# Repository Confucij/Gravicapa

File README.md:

Gravicapa
=========
Универсальное устройства для слежения за аудиториями, сбора различной информации, её обработки и отображения.

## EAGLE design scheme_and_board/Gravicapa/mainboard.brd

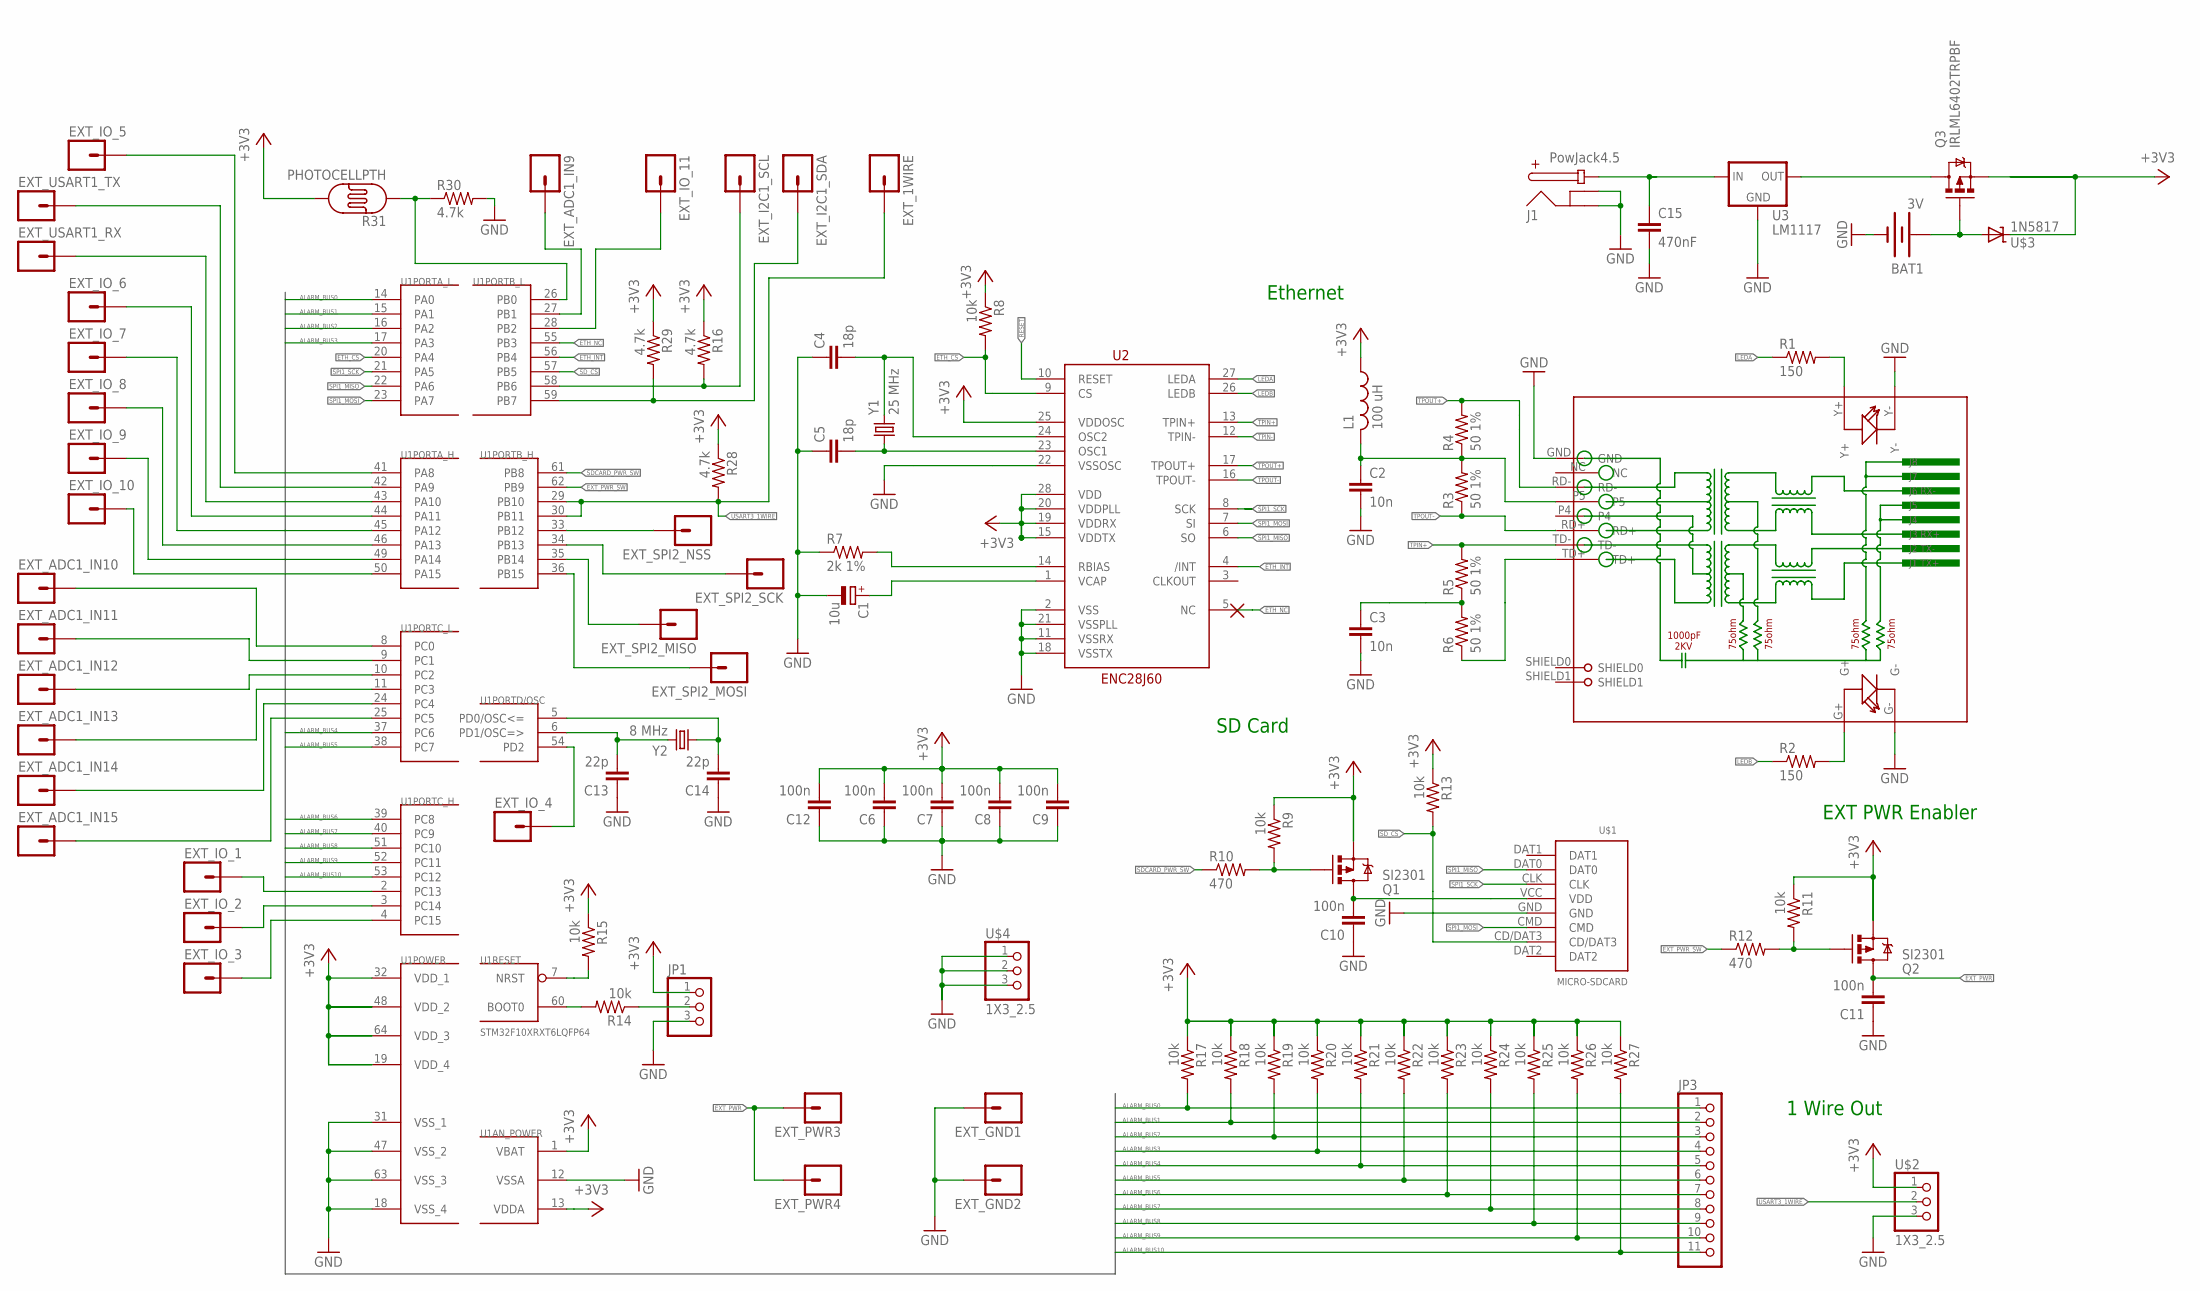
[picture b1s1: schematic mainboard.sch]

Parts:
BAT1: 3V; BATTCOM_20MM_PTH
C1: 10u; SMC_B
C2, C3: 10n; 0805
C4, C5: 18p; 0805
C6, C7, C8, C9, C10, C11, C12: 100n; 0805
C13, C14: 22p; 0805
C15: 470nF; C1206
EXT_1WIRE: M01PTH; 1X01
EXT_ADC1_IN9, EXT_ADC1_IN10, EXT_ADC1_IN11, EXT_ADC1_IN12, EXT_ADC1_IN13, EXT_ADC1_IN14, EXT_ADC1_IN15: M01PTH; 1X01
EXT_GND1, EXT_GND2: M01PTH; 1X01
EXT_I2C1_SCL, EXT_I2C1_SDA: M01PTH; 1X01
EXT_IO_1, EXT_IO_2, EXT_IO_3, EXT_IO_4, EXT_IO_5, EXT_IO_6, EXT_IO_7, EXT_IO_8, EXT_IO_9, EXT_IO_10, EXT_IO_11: M01PTH; 1X01
EXT_PWR3, EXT_PWR4: M01PTH; 1X01
EXT_SPI2_MISO, EXT_SPI2_MOSI, EXT_SPI2_NSS, EXT_SPI2_SCK: M01PTH; 1X01
EXT_USART1_RX, EXT_USART1_TX: M01PTH; 1X01
J1: PowJack4.5; POWER_JACK_4.5
JP1: PINHD-1X3; 1X03
JP3: PINHD-1X11; 1X11
L1: 100 uH; POWER-CHOKE_WE-TPC
Q1, Q2: SI2301; SOT23-3
Q3: IRLML6402TRPBF; SOT23-3
R1, R2: 150; 0805
R3, R4, R5, R6: 50 1%; 0805
R7: 2k 1%; 0805
R8, R9, R11, R13, R14, R15, R17, R18, R19, R20, R21, R22, R23, R24, R25, R26, R27: 10k; 0805
R10, R12: 470; 0805
R16, R28, R29, R30: 4.7k; 0805
R31: PHOTOCELLPTH; PHOTOCELL
RJ1: HR911105A
U1: STM32F10XRXT6LQFP64; LQFP64_MILL
U2: ENC28J60; SSOP28DB
U3: LM1117; DPAK
U$1: MICRO-SDCARD
U$2, U$4: 1X3_2.5
U$3: 1N5817; DIODE-ZENER
Y1: 25 MHz; HC49U-V
Y2: 8 MHz; HC49U-V

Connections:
+3V3: C6.2, C7.2, C8.2, C9.2, C12.2, JP1.1, L1.1, Q1.2 (S), Q2.2 (S), Q3.2 (S), R8.1, R9.1, R11.1, R13.1, R15.1, R16.1, R17.1, R18.1, R19.1, R20.1, R21.1, R22.1, R23.1, R24.1, R25.1, R26.1, R27.1, R28.1, R29.1, R31.2, U1.1 (VBAT), U1.13 (VDDA), U1.19 (VDD_4), U1.32 (VDD_1), U1.48 (VDD_2), U1.64 (VDD_3), U2.15 (VDDTX), U2.19 (VDDRX), U2.20 (VDDPLL), U2.25 (VDDOSC), U2.28 (VDD), U$2.1, U$3.P$1 (C)
ALARM_BUS0: JP3.1, R17.2, U1.14 (PA0)
ALARM_BUS1: JP3.2, R18.2, U1.15 (PA1)
ALARM_BUS2: JP3.3, R19.2, U1.16 (PA2)
ALARM_BUS3: JP3.4, R20.2, U1.17 (PA3)
ALARM_BUS4: JP3.5, R21.2, U1.37 (PC6)
ALARM_BUS5: JP3.6, R22.2, U1.38 (PC7)
ALARM_BUS6: JP3.7, R23.2, U1.39 (PC8)
ALARM_BUS7: JP3.8, R24.2, U1.40 (PC9)
ALARM_BUS8: JP3.9, R25.2, U1.51 (PC10)
ALARM_BUS9: JP3.10, R26.2, U1.52 (PC11)
ALARM_BUS10: JP3.11, R27.2, U1.53 (PC12)
ETH_CS: R8.2, U1.20 (PA4), U2.9 (CS)
ETH_INT: U1.56 (PB4), U2.4 (/INT)
ETH_NC: U1.55 (PB3), U2.5 (NC)
EXT_PWR: C11.2, EXT_PWR3.1, EXT_PWR4.1, Q2.3 (D)
EXT_PWR_SW: R12.1, U1.62 (PB9)
GND: BAT1.2 (-), C1.-, C2.2, C3.2, C4.1, C5.1, C6.1, C7.1, C8.1, C9.1, C10.1, C11.1, C12.1, C13.1, C14.1, C15.2, EXT_GND1.1, EXT_GND2.1, J1.GND@1 (GND), J1.GND@2 (GNDBREAK), JP1.3, R7.1, R30.2, RJ1.G-, RJ1.GND, RJ1.Y-, U1.12 (VSSA), U1.18 (VSS_4), U1.31 (VSS_1), U1.47 (VSS_2), U1.63 (VSS_3), U2.2 (VSS), U2.11 (VSSRX), U2.18 (VSSTX), U2.21 (VSSPLL), U2.22 (VSSOSC), U3.1 (GND), U$1.GND, U$2.3, U$4.1, U$4.2, U$4.3
I2C1_SCL: EXT_I2C1_SCL.1, R16.2, U1.58 (PB6)
I2C1_SDA: EXT_I2C1_SDA.1, R29.2, U1.59 (PB7)
LEDA: R1.1, U2.27 (LEDA)
LEDB: R2.1, U2.26 (LEDB)
unnamed: C2.1, L1.2, R3.2, R4.1, RJ1.P5
unnamed: R2.2, RJ1.G+
unnamed: R1.2, RJ1.Y+
unnamed: R7.2, U2.14 (RBIAS)
unnamed: C5.2, U2.23 (OSC1), Y1.1
unnamed: C4.2, U2.24 (OSC2), Y1.2
unnamed: C1.+, U2.1 (VCAP)
unnamed: Q2.1 (G), R11.2, R12.2
unnamed: C3.1, R5.1, R6.2
unnamed: Q1.1 (G), R9.2, R10.2
unnamed: C10.2, Q1.3 (D), U$1.VCC (VDD)
unnamed: EXT_IO_1.1, U1.2 (PC13)
unnamed: R14.2, U1.60 (BOOT0)
unnamed: JP1.2, R14.1
unnamed: R15.2, U1.7 (NRST)
unnamed: C14.2, U1.5 (PD0/OSC<=), Y2.1
unnamed: C13.2, U1.6 (PD1/OSC=>), Y2.2
unnamed: C15.1, J1.PWR, U3.3 (IN)
unnamed: EXT_IO_2.1, U1.3 (PC14)
unnamed: EXT_IO_3.1, U1.4 (PC15)
unnamed: EXT_IO_4.1, U1.54 (PD2)
unnamed: EXT_IO_5.1, U1.41 (PA8)
unnamed: EXT_USART1_TX.1, U1.42 (PA9)
unnamed: EXT_USART1_RX.1, U1.43 (PA10)
unnamed: EXT_IO_6.1, U1.44 (PA11)
unnamed: EXT_IO_7.1, U1.45 (PA12)
unnamed: EXT_IO_8.1, U1.46 (PA13)
unnamed: EXT_IO_9.1, U1.49 (PA14)
unnamed: EXT_IO_10.1, U1.50 (PA15)
unnamed: R30.1, R31.1, U1.26 (PB0)
unnamed: EXT_ADC1_IN9.1, U1.27 (PB1)
unnamed: EXT_ADC1_IN15.1, U1.25 (PC5)
unnamed: EXT_ADC1_IN14.1, U1.24 (PC4)
unnamed: EXT_ADC1_IN13.1, U1.11 (PC3)
unnamed: EXT_ADC1_IN12.1, U1.10 (PC2)
unnamed: EXT_ADC1_IN11.1, U1.9 (PC1)
unnamed: EXT_ADC1_IN10.1, U1.8 (PC0)
unnamed: BAT1.1 (+), Q3.1 (G), U$3.P$2 (A)
unnamed: EXT_IO_11.1, U1.28 (PB2)
unnamed: Q3.3 (D), U3.4 (OUT)
RESET: U2.10 (RESET)
SDCARD_PWR_SW: R10.1, U1.61 (PB8)
SD_CS: R13.2, U1.57 (PB5), U$1.CD/DAT3
SPI1_MISO: U1.22 (PA6), U2.6 (SO), U$1.DAT0
SPI1_MOSI: U1.23 (PA7), U2.7 (SI), U$1.CMD
SPI1_SCK: U1.21 (PA5), U2.8 (SCK), U$1.CLK
SPI2_MISO: EXT_SPI2_MISO.1, U1.35 (PB14)
SPI2_MOSI: EXT_SPI2_MOSI.1, U1.36 (PB15)
SPI2_NSS: EXT_SPI2_NSS.1, U1.33 (PB12)
SPI2_SCK: EXT_SPI2_SCK.1, U1.34 (PB13)
TPIN+: R5.2, RJ1.TD-, U2.13 (TPIN+)
TPIN-: R6.1, RJ1.TD+, U2.12 (TPIN-)
TPOUT+: R4.2, RJ1.RD-, U2.17 (TPOUT+)
TPOUT-: R3.1, RJ1.RD+, U2.16 (TPOUT-)
USART3_1WIRE: EXT_1WIRE.1, R28.2, U1.29 (PB10), U1.30 (PB11), U$2.2

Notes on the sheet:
Ethernet
EXT PWR Enabler
SD Card
1 Wire Out

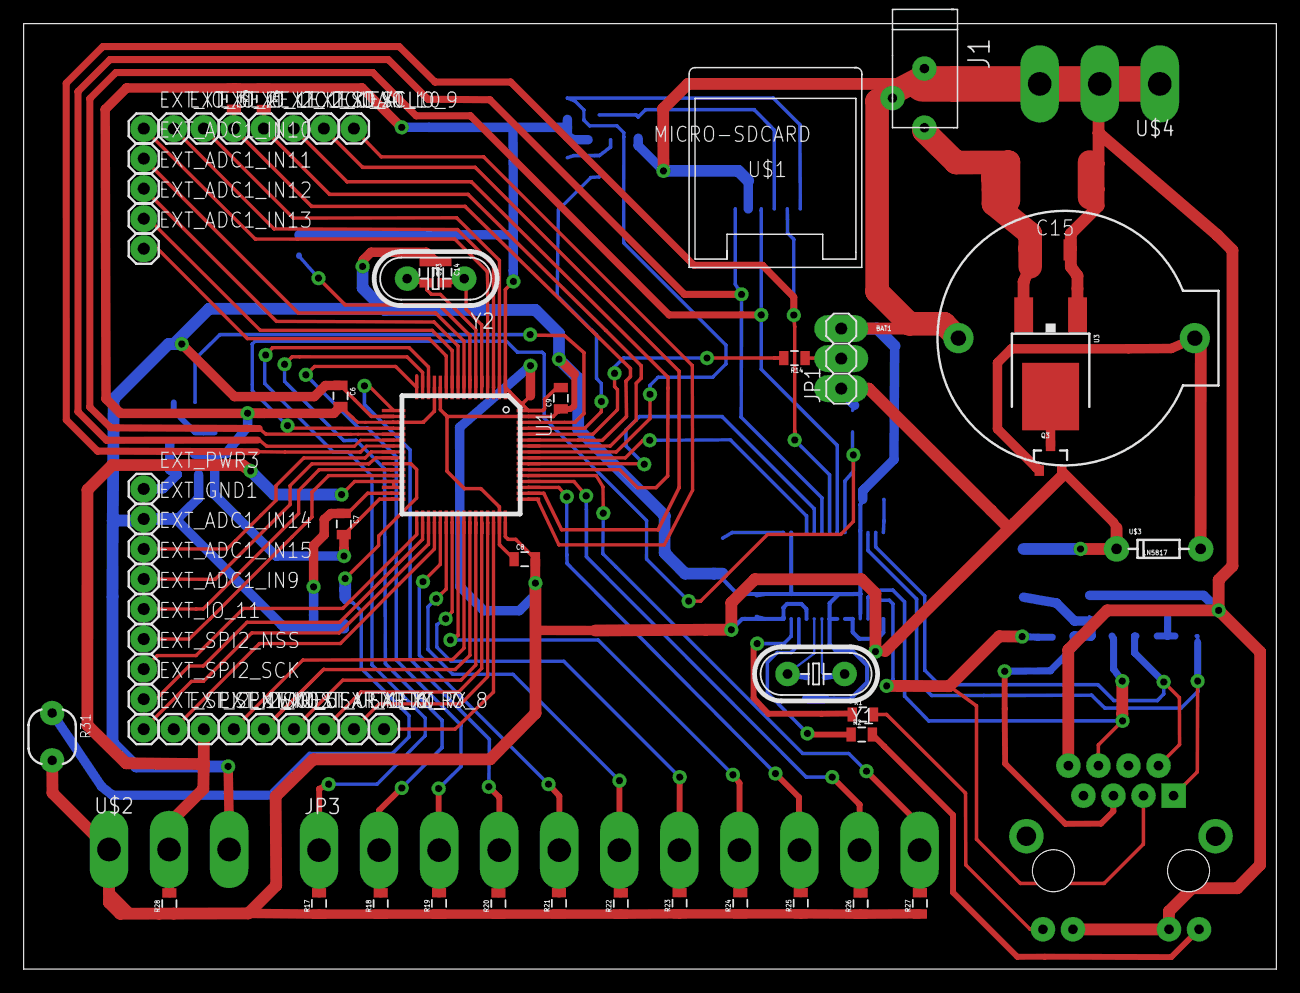
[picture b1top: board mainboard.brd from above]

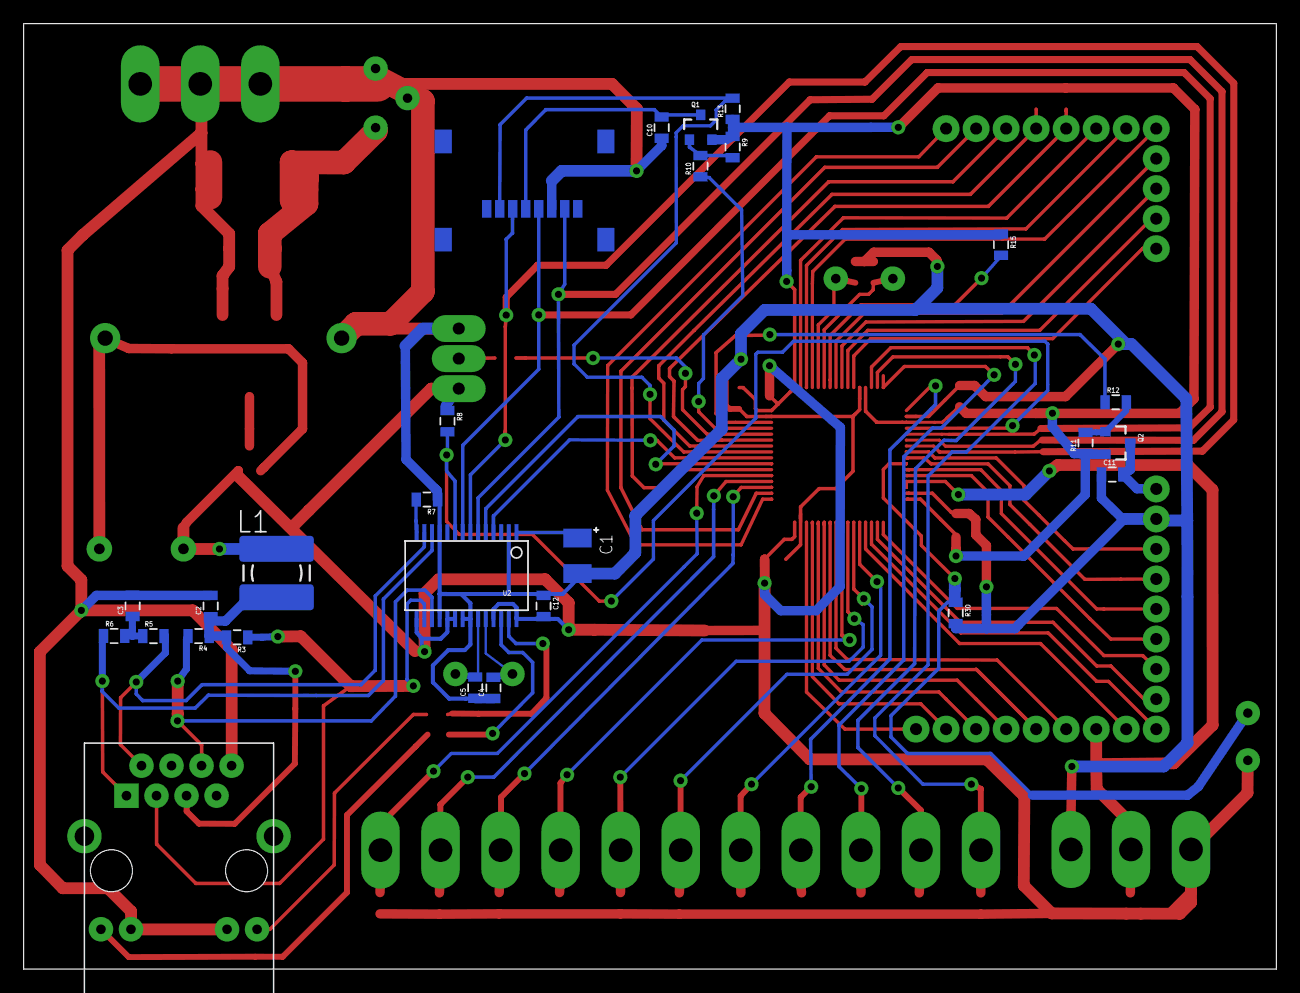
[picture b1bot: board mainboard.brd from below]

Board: 2 copper layers, 106.0 x 80.0 mm, 93 parts (26 on the bottom side), 76 nets.

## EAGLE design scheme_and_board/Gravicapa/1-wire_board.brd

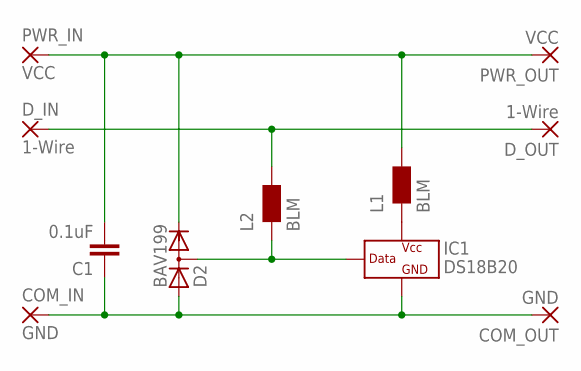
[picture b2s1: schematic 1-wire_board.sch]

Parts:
C1: 0.1uF; 0805
COM_IN: GND; SMD2,54-5,08
COM_OUT: GND; SMD2,54-5,08
D2: BAV199; SOT23
D_IN: 1-Wire; SMD2,54-5,08
D_OUT: 1-Wire; SMD2,54-5,08
IC1: DS18B20; TO92-
L1, L2: BLM; 0805
PWR_IN: VCC; SMD2,54-5,08
PWR_OUT: VCC; SMD2,54-5,08

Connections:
unnamed: D2.3 (AC), IC1.2 (DATA), L2.1
unnamed: D_IN.1, D_OUT.1, L2.2
unnamed: C1.1, COM_IN.1, COM_OUT.1, D2.1 (A), IC1.1 (GND)
unnamed: C1.2, D2.2 (C), L1.2, PWR_IN.1, PWR_OUT.1
unnamed: IC1.3 (VCC), L1.1

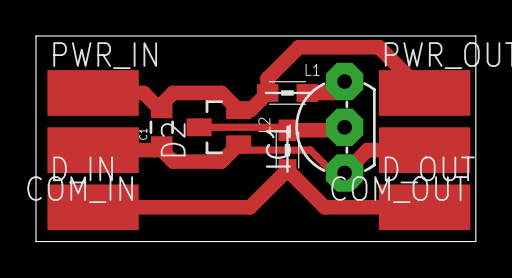
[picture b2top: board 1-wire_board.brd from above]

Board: 2 copper layers, 24.4 x 11.4 mm, 11 parts (0 on the bottom side), 5 nets.

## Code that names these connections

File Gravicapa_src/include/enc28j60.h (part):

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
//#define ENC28J60_SPI_DDR	DDRB
//#define ENC28J60_SPI_PORT	PORTB
//#define ENC28J60_SPI_CS		(1<<PB4)
//#define ENC28J60_SPI_MOSI	(1<<PB5)
//#define ENC28J60_SPI_MISO	(1<<PB6)
//#define ENC28J60_SPI_SCK	(1<<PB7)

// Init ENC28J60
void enc28j60_init(uint8_t *macadr);
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
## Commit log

2012-09-06 Выбор компонентов
2012-09-06 add folders
2012-09-06 test commit
2012-09-06 Update Component_select
2012-09-08 Изменение списка компонентов
2012-09-08 Add protocol file
2012-09-09 Добавил шаблон кода для контроллера. Включены CMSIS и StdPL, скрипт для линкера и файл стартовой инициализации. Для добавления файла из SPL в проект можно добавить его в мейкфайл или поместить в папк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
2012-09-09 TZ added
2012-09-09 Renamed to .md for markdown syntax
2012-09-09 fix TZ
2012-09-09 Добавил код драйвера Fat. Еще не тестировал.
2012-09-11 Протестировал файловую систему. Иногда работает.
2012-09-12 Проверил работу ФС - работает вроде. Режим ДМА не проверял
2012-09-12 Включил DMA. Вроди работает.
2012-09-12 Забыл добавить кусок DMA
2012-09-12 Added EAGLE library with some components, and order list
    Lib contains:
    STM32F100RBT6B
    enc28j60
    HR911105A
    CD54NP-101KC
2012-09-13 Board&Scheme, Commit 13.09
    Added some components to lib, created EagleCad project file and scheme
    file. Scheme contain enc28j60 and components related to it.
2012-09-15 Схема 15.09
2012-09-15 Добавлен PDF файл схемы, и внесены небольшие поправки
2012-09-17 Обновил библиотеку
2012-09-18 add protocol server-controlers version 0.1
2012-09-20 corrected scheme
2012-09-29 1-wire board and scheme add.
2012-09-29 Mainboard shceme modified: SPI1 NSS connected to eth_cs
2012-10-14 scheme edited. All pins used, added photosensor, interrupt pins moved for simplefing PCB. Pins for external board now are separeted for easy moving on PCB
2012-10-14 add new protocol
2012-10-21 battarey backup. Mainboard PCB. Not routed.
2012-10-23 comp order
2012-10-23 PCB in PDF format
2012-10-24 topor src added
2012-10-24 topor 1
2012-10-24 topor cleaned
2012-11-01 Order change
2012-11-02 Component...
2012-11-04 topor topor errors fixed
2012-11-28 blah blah blah
2012-11-28 Add FreeRTOS.
2012-11-28 eagle board
2012-12-02 ENC28J60 driver add.
2012-12-02 Clearing main function, changing C standart
2012-12-06 documentation protokoli i huita raznaja
2012-12-07 Add vectors table location
2012-12-08 Add isr routine for ENC and pack queue
2012-12-08 Создал две задачи: переодическую и с очередью. Включил инклюды стека
2012-12-08 Добавил к компиляции исходники стека.
2012-12-09 Valid stack pointer
2012-12-11 Receiving reg package
2012-12-13 PING and Telnet
2012-12-13 blahblah
2012-12-13 Onewire add and work(?) for 1 sensor
2012-12-14 registration work
2012-12-15 Registration and fake data send.
2012-12-16 ds18 and door works. Connection works.
2012-12-18 release 0.01a

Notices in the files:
parts and their libraries:
SparkFun: Licensing: CC v3.0 Share-Alike You are welcome to use this library for commercial purposes.
